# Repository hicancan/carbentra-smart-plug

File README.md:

<div align="center">

> 2026-10-01 classroom upgrade: the sole multi-device Edge and contract authority moved to `carbentra-campus-platform/edge` and `packages/iot-contract`. This repository owns Plug hardware, firmware and physical qualification facts. New local ON uses the same commissioning/load/feedback/dwell guards; actual presses establish a15-minute manual hold. The default target still disables actuation. Historical broker/PDF evidence does not automatically validate upgraded shared sources.

# CARBENTRA Plug

### 面向校园能源编排的 AIoT 边缘智能插座

**让普通用电设备拥有可感知、可判断、可执行、可验证的能源接口。**

[English](README_EN.md) ·
[机械工程](mechanical/rev_b/) ·
[电气工程](electronics/rev_b/integrated/) ·
[固件](firmware/) ·
[边缘服务](edge/) ·
[发布证据](release/)

</div>

本机数字验证与源码摘要见 [交付入口](release/START_HERE.md)。GitHub 徽章展示远端工作流状态；物理放行条件独立保留。

<p align="center">
  
</p>

<p align="center">
  <sub>CARBENTRA Plug Rev B · 本地数字验证快照 · 实物尚未验证</sub>
</p>

---

## 一只插座，让普通负载进入可编排能源系统

CARBENTRA Plug 是 CARBENTRA 产品体系的第一个设备终端。

它把传统电器接入一条完整的设备级闭环：

> **感知 → 校验 → 判断 → 执行 → 验证 → 回传**

电压、电流、功率、能量与温度构成设备状态；本地策略决定动作是否具备执行条件；输出反馈确认物理结果；边缘侧持久运输这些事实，平台统一完成资产绑定、预测、约束策略和能碳核算。

当一台设备接入 CARBENTRA Plug，它同时获得联网能力、可观测状态、受约束执行能力，以及一个能够被上层能源系统持续理解的数字接口。

### 四项核心能力

| 能力 | 设备侧职责 |
| --- | --- |
| **感知** | 采集电压、电流、功率、能量、板温与输出状态 |
| **保护** | 本地故障、负载档案、命令时效、序列和物理边界共同参与决策 |
| **执行** | 在本地许可通过后完成受控开关动作 |
| **验证** | 独立读取输出侧状态，把真实结果送回下一轮控制 |

**云端负责全局智能，设备守住物理边界。**

---

## 产品一览

| 项目 | Rev B 数字工程基线 |
| --- | --- |
| 产品名称 | **CARBENTRA Plug** |
| 工程型号 | **CARBENTRA-P16-EVT-B** |
| 名义外形 | **108 × 93 × 65 mm** |
| 主 PCB | **100 × 85 mm，四层** |
| 主控 | **ESP32-C3-WROOM-02U** |
| 电能计量 | **ATM90E26 + 隔离 SPI + 1 mΩ 四端分流器** |
| 机械系统 | **71 个物理机械零件** |
| 主板电气项 | **101 个电气项 + 4 个安装位** |
| 网络链路 | **Wi-Fi + MQTT 双向 TLS** 参考实现 |
| 目标接口 | **单路 220 VAC / 16 A 级设计目标** |
| 当前阶段 | **Rev B 数字工程完成，进入实物 EVT（工程验证样机）前验证阶段** |

<p align="center">
  
</p>

外壳、插孔、后部插脚、本地按钮、状态指示、主板空间、保护器件与温度拾取结构都建立在同一套工程坐标系中，并贯通 FreeCAD、KiCad、Blender 与系统装配导出。

---

# 01 · 机械系统 — 让产品在真实空间里成立

Rev B 机械工程覆盖插接结构、保护门、L/N/PE 导电路径、保险与热保护安装、PCB、远端温度拾取、后部插脚和外壳装配。

## 六视图

六视图给出产品的完整外形关系。当前工程同时提供可编辑 FreeCAD 源、STEP 总装、独立零件、公共坐标系网格、装配边界和机构检查记录。

## 爆炸结构

从外到内依次可以看到：

- 前后壳体与装配结构；
- 插孔保护门与接触机构；
- L / N / PE 导电路径；
- 保险与热保护部件；
- 四层主 PCB；
- 远端温度拾取头；
- 后部插脚与内部端接。

### 6 秒爆炸动画

<p align="center"><sub>点击动画预览可打开原始 MP4。</sub></p>

## 剖视图

剖视图展示机械插接结构、电源路径、主板、保护器件与感知部件在封闭体积中的真实相对关系，并与系统总装使用同一坐标基准。

工程源文件：

- [FreeCAD 系统总装](mechanical/rev_b/CARBENTRA-P16-EVT-B_system_assembly.FCStd)
- [机械 STEP](mechanical/rev_b/CARBENTRA-P16-EVT-B_mechanical.step)
- [详细系统 STEP](mechanical/rev_b/CARBENTRA-P16-EVT-B_system_detailed.step)
- [机械验证摘要](mechanical/rev_b/VALIDATION_SUMMARY.md)

---

# 02 · 电气系统 — 把计量、控制、保护与反馈收进同一块主板

CARBENTRA Plug 的电气设计围绕一条明确主线展开：

> **测得准 · 隔得开 · 控得住 · 看得到结果 · 故障时保留本地保护**

<p align="center">
  
</p>

Rev B 已经整合以下功能域：

- IRM-10-5 隔离 5 V 电源与 AP63203 3.3 V 逻辑电源；
- ESP32-C3 主控、编程接口、本地按钮、状态指示与外置天线接口；
- ATM90E26 电能计量链路、1 mΩ 四端分流器与隔离 SPI；
- 输出侧 AC presence 独立反馈；
- 远端 TMP302 温度阈值链路、锁存与本地物理复位；
- 主保险、热保护、继电器与输出路径；
- 连续 PE 保护导体路径。

## 原理图

**点击上图打开完整原理图 PDF。**

README 总览采用中文功能页名称；元件位号、网络名与工程信号名保留 KiCad 原始命名，方便直接对应设计源文件。

六个功能页面：

[系统总览](electronics/rev_b/integrated/exports/integrated.svg) ·
[主控与通信](electronics/rev_b/integrated/exports/integrated-1%20controller.svg) ·
[电能计量](electronics/rev_b/integrated/exports/integrated-2%20meter.svg) ·
[输出状态反馈](electronics/rev_b/integrated/exports/integrated-3%20feedback.svg) ·
[热保护链](electronics/rev_b/integrated/exports/integrated-4%20thermal.svg) ·
[装配与一级保护](electronics/rev_b/integrated/exports/integrated-5%20assembly%20protection.svg)

KiCad 原生工程：

[`electronics/rev_b/integrated/`](electronics/rev_b/integrated/)

## 四层 PCB

Rev B 主板采用 **100 × 85 mm 四层设计**。当前数字检查记录：

- DRC 违规：**0**
- 未连接项：**0**
- 封装错误：**0**
- ERC 错误 / 警告：**0 / 0**
- 原理图—PCB 独立引脚键对照：**321 / 321 一致**

上图按照 **顶层 F.Cu / 内层一 In1.Cu / 内层二 In2.Cu / 底层 B.Cu** 展示当前铜层。点击可打开完整铜层审阅 PDF。

## PCB 装配

PCB 视觉装配直接由当前 ECAD 导出进入机械总装与 Blender 展示场景，实现原理图、PCB、机械结构和视觉资产之间的连续追踪。

进一步查看：

- [KiCad 原生工程](electronics/rev_b/integrated/integrated.kicad_pro)
- [电气 BOM](electronics/rev_b/integrated/electrical_bom.csv)
- [电气设计定义](electronics/rev_b/integrated/ELECTRICAL_SOURCE.md)
- [功率与电流复核](electronics/rev_b/integrated/POWER_CURRENT_REVIEW.md)
- [最终电气验证摘要](electronics/rev_b/integrated/validation/final_summary.json)

---

# 03 · 固件控制 — 把每一次物理动作放进本地安全上下文

CARBENTRA Plug 会在设备端重新判断每一条控制请求。

控制链依次检查：

- 设备身份与目标；
- 命令时间边界与 TTL；
- 命令序列与重放；
- 当前负载档案；
- 本地故障锁存；
- 计量数据有效性；
- 动作间隔与当前物理状态；
- 输出反馈与请求状态的一致性。

### 三条核心原则

1. **本地安全拥有最高执行优先级。**
2. **过期、重放、错目标和异常格式命令直接拒绝。**
3. **未知或未批准负载进入仅监测状态。**

当前固件代码已经覆盖：

- C 策略核心；
- ATM90E26 采集与完整性检查；
- TMP102 板温采集；
- AC presence 边沿反馈；
- Wi-Fi 重连；
- BLE 安全配网路径；
- MQTT 双向 TLS；
- retained 消息、分片、长度、类型与重复键边界检查；
- NVS 持久命令序号；
- 有界 RAM 遥测缓冲；
- 边缘侧持久化回执语义。

## 可复现软件检查

```powershell
uv venv --python 3.12
uv sync --locked
$env:CARBENTRA_PLATFORM_ROOT='D:\code\github\hicancan\carbentra-suite\carbentra-campus-platform'
pwsh -NoProfile -File scripts/check_windows.ps1 -OutputDirectory 'D:\Temp\codex\carbentra-plug-check' -BuildTarget
```

本机环境、原生 CAD 重建顺序与工具路径见 [Windows 开发说明](docs/WINDOWS_DEVELOPMENT.md)。

Windows 入口会自动编译真实 Switch C 解码器，并将它与三个 Plug C 验证器
一起传入共享 Edge 的 `--release` 门禁。默认从同级的共享平台及 Switch 仓取源；
不同目录可传 `-PlatformRoot`、`-SwitchRoot`。编译入口是共享平台的
`edge/tests/c/switch_command_decoder.c`，链接 Switch 的
`firmware/core/switch_core.c`、`firmware/main/command_json.c` 与 SDK 固定版本
cJSON，构建记录保存源文件及程序 SHA-256。该程序只解析命令行 JSON，
退出码 0/1 分别表示接受/拒绝，没有设备或网络操作。需要复用已编译程序时，
仍可显式传 `-SwitchCommandTestBinary`；缺失或失败不会降级为跳过。
Linux `run_development_checks.sh` 和独立完整 release 验证器仍要求
`CARBENTRA_SWITCH_COMMAND_TEST_BINARY`。CAD 或场景改变时，再加
`-CheckNativeCAD -RenderGPU`；Windows 通过不会自动更新历史 Linux/CAD 证明。

[本次固件复验](firmware/remediation-report.json)记录全新 ESP-IDF 5.4.3 目标构建、
host 安全回归和新增共享解码器门禁的传递检查。它不修改原有实物 HOLD 状态，
也不把历史 CAD/制造报告重新标为本次运行。

当前仓库已验证：

- 唯一 C 本地保护核心，**45** 个策略用例；
- 边缘发布门禁记录 OS 专属排除与互补验证，当前测试数量见 firmware/evidence/shared-edge-validation.json；
- **10,000** 次本地故障优先级不变量检查；
- 协议 / 计量复位 / 链路卡滞回归；
- 输出反馈判定测试；
- 已配置 GitHub Actions Windows 主机门禁和 ESP32-C3 目标构建；远端执行状态以 Actions 记录为准。

ESP32-C3 当前源码已使用官方 ESP-IDF 5.4.3 重新构建，默认继电器禁用、证书有效期校验启用；源码与产物摘要见 firmware/validation.json。真实硬件验证仍为 HOLD。

---

# 04 · 边缘协同 — 把设备事实沉淀成楼宇侧状态

设备把测量与执行结果交给边缘节点，边缘节点将它们组织成可以持续协调的楼宇侧状态。

共享平台仓库中的边缘服务提供：

- MQTT 设备适配；
- 允许清单与设备身份校验；
- SQLite WAL 持久化；
- 启动纪元 + 序号去重；
- 持久化回执；
- 控制回执保存；
- 带重试和冲突隔离的 HTTP outbox；
- 持久命令 inbox、租约、过期/重放守卫和独立物理放行门；
- 源摘要绑定的真实软件 broker / 平台联调。预测、调度和核算只有平台一份实现。

一条设备遥测在成功落库后返回持久化回执，由此可以清晰区分“消息已到达 MQTT 消息代理”和“数据已进入边缘状态库”。

[查看边缘参考服务](edge/README.md)

---

# 05 · 云边端协同 — 从一个设备节点扩展到一组可协调负载

当设备端的感知、执行和反馈闭环成立，多台 CARBENTRA Plug 就可以进入更高层的能源协调。

系统分工：

- **CARBENTRA Plug**：感知、保护、执行、验证；
- **CARBENTRA Edge**：合同校验、持久收据、重试运输、命令网关；
- **CARBENTRA Cloud**：负荷预测、约束策略评估、全局调度；
- **CARBENTRA Twin**：映射设备、空间、能耗、碳排与执行状态。

> **一只 Plug 让一台设备可被控制；一组 Plug 让一片负载可以被协同。**

CARBENTRA Plug 位于能源算法与真实物理设备之间，把调度策略落到最后一米，并把执行结果重新送回系统。

---

## 工程进度

| 领域 | 当前状态 |
| --- | --- |
| 产品定义 | ✅ CARBENTRA Plug Rev B 数字基线 |
| 机械 CAD | ✅ 原生 CAD + STEP + 装配 / 机构 / 连通性证据 |
| 电气设计 | ✅ 六页原理图 + 四层 PCB + ERC / DRC 数字检查 |
| 固件主机逻辑 | ✅ 策略、协议、反馈、计量回归测试 |
| 边缘参考服务 | ✅ 严格合同、持久运输、mTLS 虚拟设备闭环 |
| 视觉 / 数字孪生资产 | ✅ Blender、GLB、渲染、爆炸动画 |
| ESP32-C3 新版目标二进制 | ✅ 官方 ESP-IDF 5.4.3 当前源码实际构建，继电器禁用 |
| 实物 EVT（工程验证样机） | ⏳ 下一阶段 |
| 逐台计量标定 | ⏳ 实物阶段 |
| 16 A 温升 / 故障验证 | ⏳ 实物阶段 |
| 绝缘 / EMC / 浪涌 / 安规 | ⏳ 专业审查与试验阶段 |
| 校园现场闭环 | ⏳ EVT 与安全放行后进入 |

完整工程放行条件：

[`docs/ENGINEERING_RELEASE_GATES.md`](docs/ENGINEERING_RELEASE_GATES.md)

---

## 打开工程

### 机械工程

```text
mechanical/rev_b/
├── CARBENTRA-P16-EVT-B.FCStd
├── CARBENTRA-P16-EVT-B_mechanical.step
├── CARBENTRA-P16-EVT-B_system_assembly.FCStd
├── CARBENTRA-P16-EVT-B_system_assembly.step
├── CARBENTRA-P16-EVT-B_system_detailed.step
├── parts/
├── meshes/
└── validation reports...
```

### 电气工程

```text
electronics/rev_b/integrated/
├── integrated.kicad_pro
├── integrated.kicad_sch
├── integrated.kicad_pcb
├── electrical_bom.csv
├── electrical_manifest.json
├── exports/
└── validation/
```

### 固件与边缘服务

```text
firmware/
├── core/
├── main/
├── tests/
├── tools/
└── validation.json

edge/
├── README.md        # shared implementation: carbentra-campus-platform/edge
└── PROVENANCE.json  # migration record
```

### 视觉与数字孪生

```text
visuals/rev_b/
├── carbentra_studio.blend
├── carbentra_animation.blend
├── exports/
│   ├── carbentra_assembly.glb
│   └── carbentra_twin_light.glb
├── renders/
└── animation/
```

---

## 仓库结构

```text
carbentra-smart-plug/
├── mechanical/      # CAD、STEP、零件、机构与装配检查
├── electronics/     # KiCad 原理图、PCB、BOM、电气验证
├── firmware/        # ESP32-C3 源码、策略、计量、网络与主机测试
├── edge/            # 平台共享 Edge 的迁移说明与来源记录
├── visuals/         # Blender、渲染、GLB、动画
├── docs/            # 系统契约、品牌体系与平台叙事
├── tests/           # 策略参考测试
├── scripts/         # 验证与发布工具
└── release/         # 数字工程发布证据与审阅材料
```

按照工程审阅顺序阅读时，可以从 [`release/START_HERE.md`](release/START_HERE.md) 开始。

---

## 从数字工程走向实物 EVT

当前 Rev B 已经把机械、电气、固件、边缘服务和视觉资产收敛到同一套数字工程基线。下一阶段将把这些设计结论逐项落到实物验证：

- 目标市场对应的插头 / 插座标准确认；
- 实际爬电距离、空气间隙与绝缘结构审核；
- 外壳材料与异常工况验证；
- 预期故障电流与保护配合；
- 16 A 封闭温升与连接点发热试验；
- 插接量规、接触力、寿命、保持力与保护门验证；
- 不同负载类型的浪涌与继电器开断能力测试；
- 电压、电流、功率、能量逐台可溯源标定；
- 浪涌 / EFT / EMC / RF 集成测试；
- 生产级设备身份、安全启动、升级与密钥配置；
- 受控实物 EVT 与真实场景闭环验证。

> [!WARNING]
> **220 VAC / 16 A 级接口目前属于设计目标。实物额定能力、制造放行与产品合规将在上述验证完成后确定。**

---

## 项目与品牌

**CARBENTRA Plug** 是 CARBENTRA 产品体系中的首个设备终端。

```text
碳迹未来
└── CARBENTRA
    ├── CARBENTRA Plug      ← 本仓库
    ├── CARBENTRA Sense
    ├── CARBENTRA Edge
    ├── CARBENTRA Cloud
    └── CARBENTRA Twin
```

比赛 / 项目名称：

> **碳迹未来——基于 AIoT 云边端协同的高校智慧能碳管理平台**

平台英文描述：

> **CARBENTRA — AIoT Campus Energy Orchestration Platform**

完整平台叙事：

[**docs/PLATFORM_OVERVIEW.md**](docs/PLATFORM_OVERVIEW.md)

---

<div align="center">

# CARBENTRA Plug

### **Sense · Protect · Execute · Verify**

**让普通设备进入可编排的能源系统。**

[English README](README_EN.md)

</div>

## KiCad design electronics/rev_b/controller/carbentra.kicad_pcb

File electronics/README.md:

# CARBENTRA electronic development release

## What exists

Editable KiCad 9 schematic and two-layer 72×68 mm PCB; upstream-symbol-derived pin geometry; 33 placed electrical components plus 4 mounting holes (37 footprints); real net assignments; fully connected isolated low-voltage routing (digital connectivity only); true KiCad ERC/DRC reports; BOM candidate sources; board/package STEP, FreeCAD and OBJ; regenerated PDF/SVG review drawings. This is a **development source release with FABRICATION HOLD**, not a finished appliance circuit or a safe prototype to energize.

Main controller: ESP32-C3-WROOM-02U-N4 with external antenna connector, 5 V isolated supply candidate, 3.3 V synchronous buck, relay MOSFET/flyback network and digital board temperature sensor, physical local pushbutton and status LED. GPIO 18/19 are allocated to these controls, so native USB is not available on this revision. Main switching candidate is TE RT314005 5 V coil. Mains input/output/fused-auxiliary nets are intentionally unrouted. The right-hand LV routing region is digitally connected and DRC-checked, not a verified EMC/power integrity layout.

A real external antenna candidate and a mechanical pocket are defined in `PROTECTION_AND_RF.md`. Check module integration approvals and qualify range with enclosure/contact metal. The MCU variant is 02U, with an external antenna.

## Files

- `carbentra.kicad_sch`, `.kicad_pcb`, `.kicad_pro`, `.kicad_dru`: editable source and preliminary constraints
- `CARBENTRA.kicad_sym`, `sym-lib-table`: local symbols, flattened from installed KiCad library for portability
- `circuit_manifest.json`: machine-readable pins, nets, placements and schematic positions
- `bom.csv`: candidates, NOT a purchase-approved BOM; passives require precise grade/voltage/package selection
- `METERING_DESIGN.md`: substantive isolated metering boundary, pin map and sizing; daughterboard NOT implemented
- `validation/`: actual ERC, DRC, routing and geometric validation outputs
- `exports/`: review-only models/drawings
- `scripts/build_electronics.py`: regenerate source (overwrites board routing)
- `scripts/route_lv.py`: attempt LV routing, always follow with real DRC
- `scripts/export_geometry.py`: nominal package envelopes + board/footprint pad visualization

## Functional and power assumptions

IRM-03-5 candidate supplies 5 V/0.6 A. A 0.403 W relay coil consumes about 81 mA. An assumed 0.5 A peak 3.3 V controller load at 85% buck efficiency draws 388 mA from 5 V, leaving about 131 mA before other loads and supply derating. This is a preliminary budget, not measured. Include metering isolation power and all transients before final selection; verify rail dips during simultaneous radio transmission/relay actuation. Buck capacitor effective capacitance must account for DC bias, and high-current loop/switch-node layout requires review.

AP63203 pins: 1 FB → 3.3 V; 2 EN → 5 V; 3 IN → 5 V; 4 GND; 5 SW; 6 BST. Q1 is AO3400A, with manufacturer maximum RDS(on) of 48 mΩ at 2.5 V gate drive. Its pins are 1 gate, 2 source to ground, 3 drain to coil-low. D1 cathode connects to 5 V and anode to coil-low. R2 holds the gate low when the MCU is high-impedance; it is not an independent safety channel. Relay contact 11 is common, 14 is normally open, and 12 is externally unused but remains a hazardous live terminal when the relay is de-energized; it is assigned L_NC_UNUSED for clearance checking. A welded contact cannot be made safe by firmware.

Cold boot / loss of control power de-energizes this monostable relay. Runtime unknown-load handling is monitor-only; stale data rejects new automatic commands and holds the commissioned state, as specified in the system reference model. Hardware fault interruption, watchdog policy and power-restoration behavior must be commissioned by load category. This board does not implement a universal abrupt shutdown policy.

## Mains and PE

Target: 220 V nominal, 16 A-class single polarized socket. Actual continuous current, branch protection, terminal rating, contact category and operating temperature remain unqualified. **16 A resistive relay rating does not establish air-conditioner/compressor/motor, transformer or capacitive-inrush capability.** Profile software cannot uprate contacts or copper. Unknown loads are monitor-only for automatic energy management; known load categories still require validated hardware limits.

J1, J2 and J5 use Phoenix MKDS 3/2-5.08, part 1711725, with the matching KiCad footprint. Its 24 A nominal rating is a component rating, not this product's released continuous-current rating. Confirm the final conductor, torque, support, temperature rise and strain relief. High-current copper is absent: copper weight, width, neck-downs, solder joints and fault let-through must be engineered before routing. Do not bridge the airwires and energize.

Real main/auxiliary fuse and independent thermal-cutoff candidates are now dimensioned in `PROTECTION_AND_RF.md` and allocated mechanically; their electrical/harness integration and coordination are not validated. Surge network and any required snubber remain incomplete. They require ratings, layout, failure-mode analysis and system-level testing. A fuse is not an over-temperature sensor; a MOV alone is not complete surge protection.

PE bypasses this PCB in an uninterrupted stamped/wired protective path and must never be switched, fused or routed through the MCU ground. Mechanical PE continuity solids are not proof of actual earth-bond resistance, retention or contact force. Never assume N is safe to touch; polarity/reversal fault analysis and all-pole disconnection requirements depend on final product category.

## Review gates before any hardware build

- [ ] Choose target jurisdiction, plug/socket dimensional standard, accessible-part class, temperature range and required compliance tests
- [ ] Complete all mains/protection/metrology circuits and independent thermal safety; produce fault tree and critical-component list
- [ ] Resolve all KiCad unconnected nets and DRC violations without suppressing safety failures
- [ ] Verify every manufacturer pin/footprint drawing, exact suffix, BOM source and symbol connectivity independently
- [ ] Confirm required clearance/creepage from applicable standards; 8 mm rule is an explicitly preliminary engineering target, not a compliance conclusion
- [ ] Validate all copper currents/temperature rises, conductor/terminal retention, PE bond and short-circuit withstand
- [ ] Complete external antenna and metering daughterboard mechanical allocations, wiring paths, connectors and controls
- [ ] Test surge/EFT/ESD/EMI, dielectric/impulse, leakage, abnormal temperature, relay endurance and welded-contact behavior in a qualified lab
- [ ] Verify watchdog, brownout, cold-boot de-energization, stale-data command rejection, offline commissioned-state hold and secure signed firmware behavior
- [ ] Release only after independent electrical/safety review and documented manufacturer acceptance

No Gerber/drill set is supplied because it would misleadingly imply fabrication readiness. Reports may be clean in one domain while the design remains incomplete and unsafe to power.

## Final digital verification

ERC: **0 errors, 0 warnings**. PCB DRC: **0 geometric violations**, **0 low-voltage airwires**, **9 intentional mains-domain airwires**. All 104 assigned pins match the exported schematic netlist and PCB pads. See `validation/final_summary.json` and the complete, unfiltered reports. DRC success does not remove fabrication hold: the mains circuit remains physically incomplete and the metering daughterboard is not implemented.

The final board has 729 routed segments, 85 vias and 2 ground zones. These establish digital connectivity, not safe current capacity, EMC performance, transient integrity, or protection behavior. No embedded firmware has been flashed or exercised on hardware.

KiCad library symbol geometry is attributed to the KiCad Community under its library licence and design exception; see `KICAD_LIBRARY_LICENSE.txt`.

## Rebuild and system interfaces

Run `bash scripts/rebuild.sh` with KiCad 9 and its Python bindings installed. It regenerates placement and schematic, checks fixed geometry, then replays the reviewed completed-LV copper recipe. Do not rerun the experimental autorouting helpers on the finished board. Exporting package STEP/OBJ also requires FreeCAD Python; `scripts/export_geometry.py` handles it.

For the Wi-Fi/BLE deployment boundary, sensor ownership and exact runtime unknown/stale-data behavior, see [wireless networking and sensors](../docs/system/network-and-sensors.md) and [system requirements](../docs/system/README.md). The PCB includes board temperature sensing, not a complete hot-contact telemetry path. Independent relay/output-state feedback and the metering daughterboard remain incomplete.

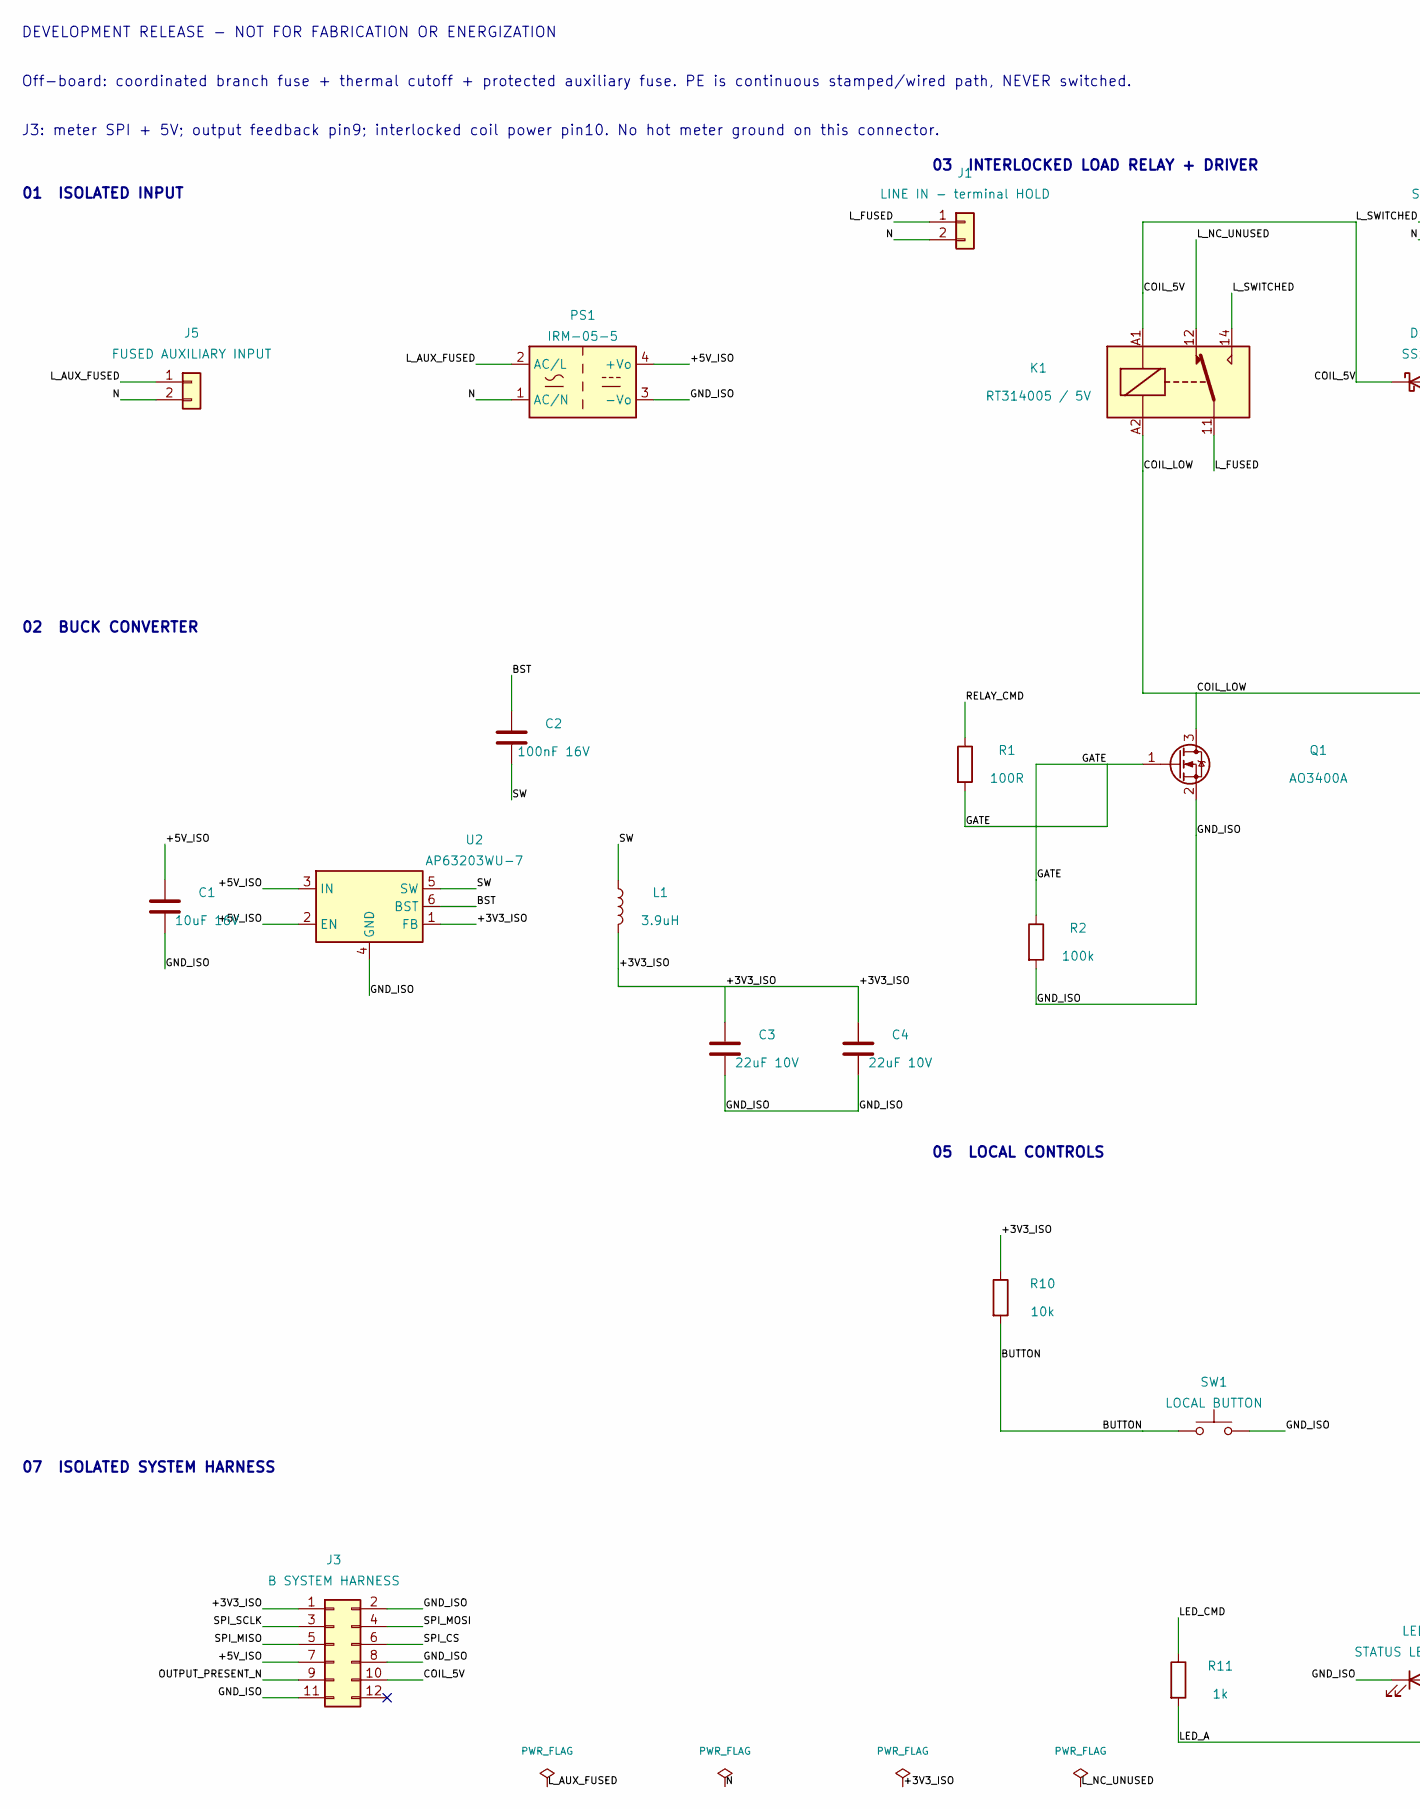
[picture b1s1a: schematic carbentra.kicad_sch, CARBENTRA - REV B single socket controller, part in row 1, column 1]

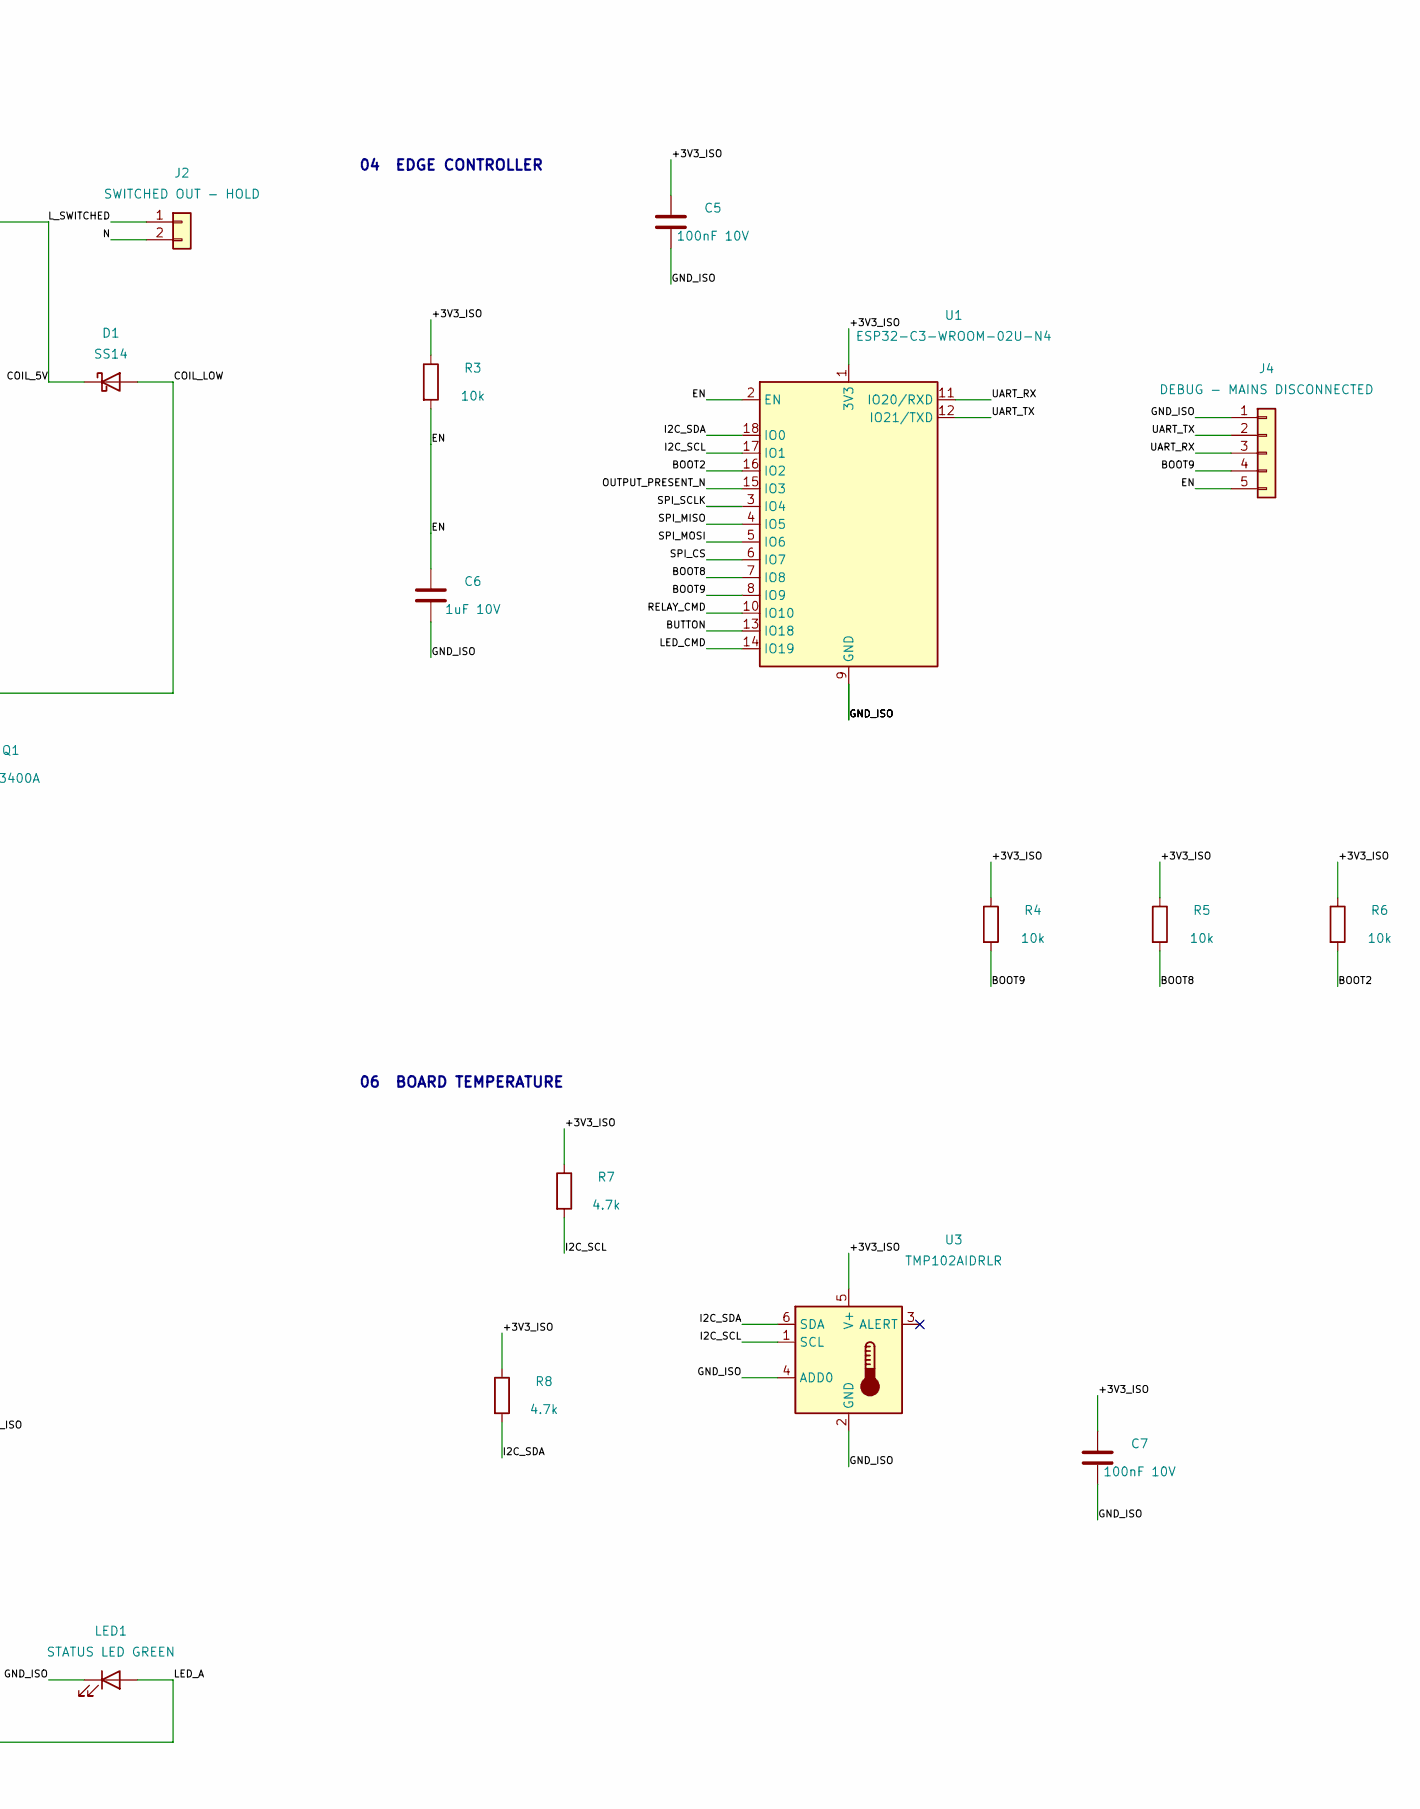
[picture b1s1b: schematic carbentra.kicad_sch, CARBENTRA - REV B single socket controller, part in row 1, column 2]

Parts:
C1: 10uF 16V; C_0805_2012Metric
C2: 100nF 16V; C_0805_2012Metric
C3, C4: 22uF 10V; C_0805_2012Metric
C5, C7: 100nF 10V; C_0805_2012Metric
C6: 1uF 10V; C_0805_2012Metric
D1: SS14; D_SMA
J1: LINE IN - terminal HOLD; TerminalBlock_Phoenix_MKDS-3-2-5.08_1x02_P5.08mm_Horizontal
J2: SWITCHED OUT - HOLD; TerminalBlock_Phoenix_MKDS-3-2-5.08_1x02_P5.08mm_Horizontal
J3: B SYSTEM HARNESS; PinHeader_2x06_P2.54mm_Vertical
J4: DEBUG - MAINS DISCONNECTED; PinHeader_1x05_P2.54mm_Vertical
J5: FUSED AUXILIARY INPUT; TerminalBlock_Phoenix_MKDS-3-2-5.08_1x02_P5.08mm_Horizontal
K1: RT314005 / 5V; Relay_SPDT_Schrack-RT1-16A-FormC_RM5mm
L1: 3.9uH; L_Bourns-SRN4018
LED1: STATUS LED GREEN; LED_D3.0mm
PS1: IRM-05-5; Converter_ACDC_MeanWell_IRM-05-xx_THT
Q1: AO3400A; SOT-23
R1: 100R; R_0603_1608Metric
R2: 100k; R_0603_1608Metric
R3, R4, R5, R6, R10: 10k; R_0603_1608Metric
R7, R8: 4.7k; R_0603_1608Metric
R11: 1k; R_0603_1608Metric
SW1: LOCAL BUTTON; SW_PUSH_6mm
U1: ESP32-C3-WROOM-02U-N4; ESP32-C3-WROOM-02U
U2: AP63203WU-7; TSOT-23-6
U3: TMP102AIDRLR; SOT-563

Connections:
+3V3_ISO: C3.1, C4.1, C5.1, C7.1, J3.1, L1.2, R3.1, R4.1, R5.1, R6.1, R7.1, R8.1, R10.1, U1.1 (3V3), U2.1 (FB), U3.5 (V+)
+5V_ISO: C1.1, J3.7, PS1.4 (+Vo), U2.2 (EN), U2.3 (IN)
BOOT2: R6.2, U1.16 (IO2)
BOOT8: R5.2, U1.7 (IO8)
BOOT9: J4.4, R4.2, U1.8 (IO9)
BST: C2.1, U2.6 (BST)
BUTTON: R10.2, SW1.1, U1.13 (IO18)
COIL_5V: D1.1 (K), J3.10, K1.A1
COIL_LOW: D1.2 (A), K1.A2, Q1.3 (D)
EN: C6.1, J4.5, R3.2, U1.2 (EN)
GATE: Q1.1 (G), R1.2, R2.1
GND_ISO: C1.2, C3.2, C4.2, C5.2, C6.2, C7.2, J3.2, J3.8, J3.11, J4.1, LED1.1 (K), PS1.3 (-Vo), Q1.2 (S), R2.2, SW1.2, U1.9 (GND), U1.19 (GND), U2.4 (GND), U3.2 (GND), U3.4 (ADD0)
I2C_SCL: R7.2, U1.17 (IO1), U3.1 (SCL)
I2C_SDA: R8.2, U1.18 (IO0), U3.6 (SDA)
LED_A: LED1.2 (A), R11.2
LED_CMD: R11.1, U1.14 (IO19)
L_AUX_FUSED: J5.1, PS1.2 (AC/L)
L_FUSED: J1.1, K1.11
L_NC_UNUSED: K1.12
L_SWITCHED: J2.1, K1.14
N: J1.2, J2.2, J5.2, PS1.1 (AC/N)
OUTPUT_PRESENT_N: J3.9, U1.15 (IO3)
RELAY_CMD: R1.1, U1.10 (IO10)
SPI_CS: J3.6, U1.6 (IO7)
SPI_MISO: J3.5, U1.4 (IO5)
SPI_MOSI: J3.4, U1.5 (IO6)
SPI_SCLK: J3.3, U1.3 (IO4)
SW: C2.2, L1.1, U2.5 (SW)
UART_RX: J4.3, U1.11 (IO20/RXD)
UART_TX: J4.2, U1.12 (IO21/TXD)

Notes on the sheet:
DEVELOPMENT RELEASE - NOT FOR FABRICATION OR ENERGIZATION
Off-board: coordinated branch fuse + thermal cutoff + protected auxiliary fuse. PE is continuous stamped/wired path, NEVER switched.
J3: meter SPI + 5V; output feedback pin9; interlocked coil power pin10. No hot meter ground on this connector.
01 ISOLATED INPUT
02 BUCK CONVERTER
03 INTERLOCKED LOAD RELAY + DRIVER
04 EDGE CONTROLLER
05 LOCAL CONTROLS
06 BOARD TEMPERATURE
07 ISOLATED SYSTEM HARNESS

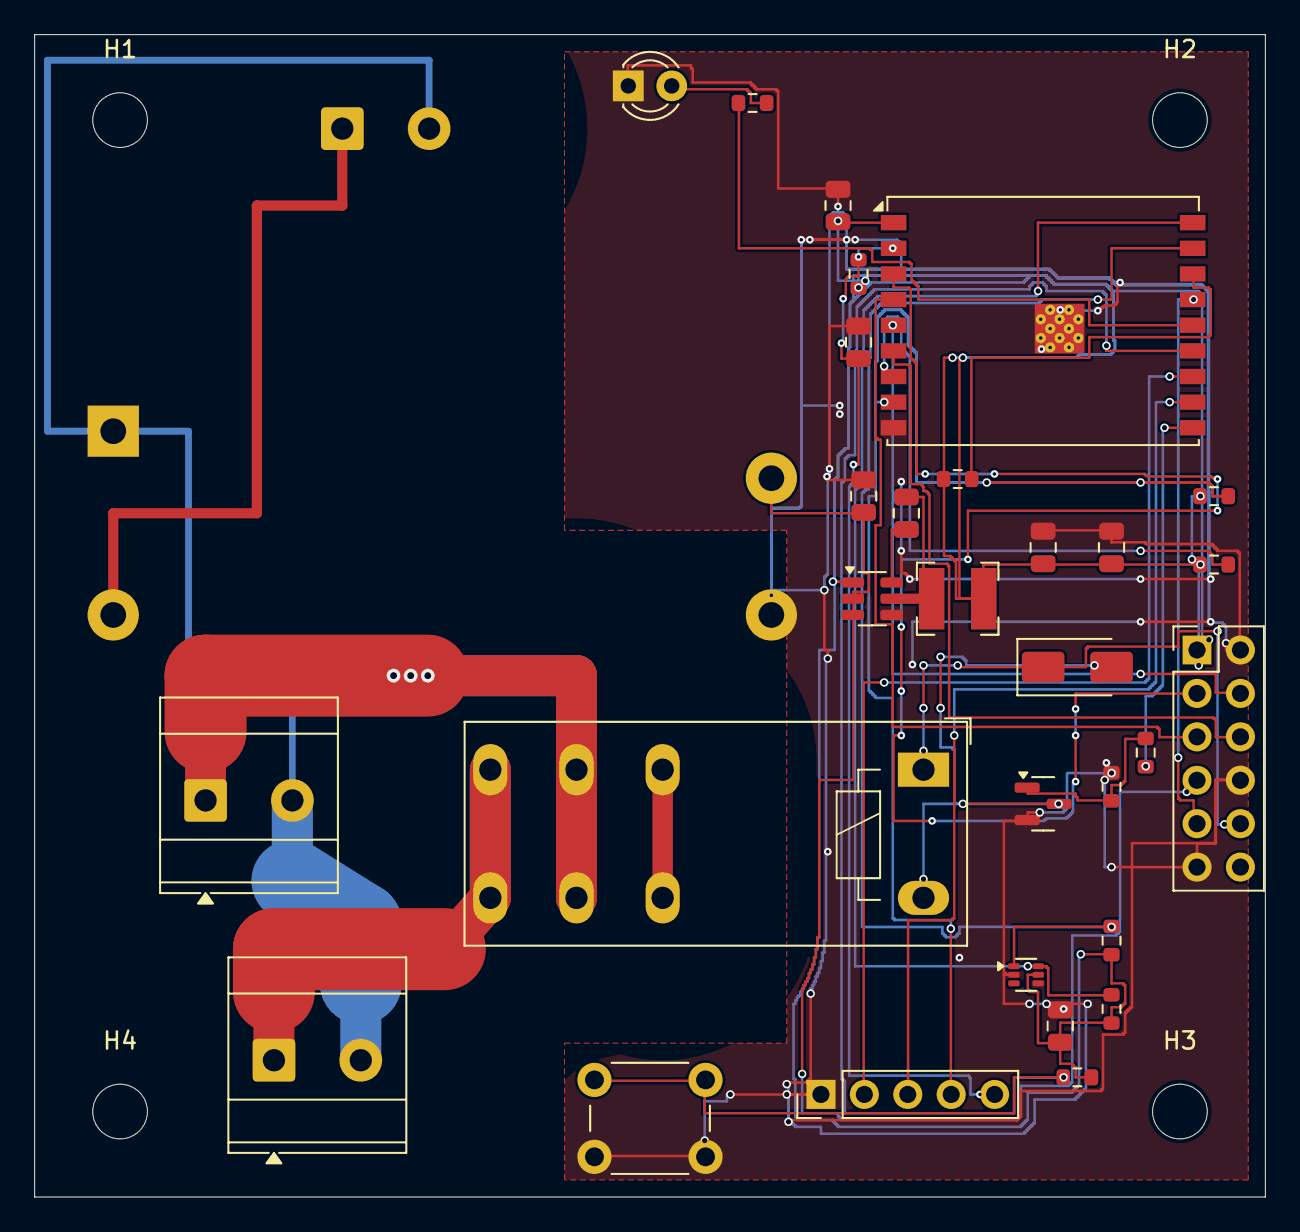
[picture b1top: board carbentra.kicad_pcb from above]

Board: 2 copper layers, 72.0 x 68.0 mm, 36 parts (0 on the bottom side), 29 nets.

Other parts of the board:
H1, H2, H3, H4: MountingHole_3.2mm_M3

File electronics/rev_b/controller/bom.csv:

Reference,Value,Manufacturer part candidate,Footprint,Source URL,Status
PS1,IRM-05-5,IRM-05-5,Converter_ACDC:Converter_ACDC_MeanWell_IRM-05-xx_THT,https://www.meanwell.com/Upload/PDF/IRM-05/IRM-05-SPEC.PDF,"UNRELEASED: verify exact variant, sourcing and application"
K1,RT314005 / 5V,RT314005 / 1-1649328-0,Relay_THT:Relay_SPDT_Schrack-RT1-16A-FormC_RM5mm,https://www.te.com/en/product-1-1649328-0.html,"UNRELEASED: verify exact variant, sourcing and application"
U1,ESP32-C3-WROOM-02U-N4,ESP32-C3-WROOM-02U-N4,RF_Module:ESP32-C3-WROOM-02U,https://www.espressif.com/sites/default/files/documentation/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,"UNRELEASED: verify exact variant, sourcing and application"
U2,AP63203WU-7,AP63203WU-7,Package_TO_SOT_SMD:TSOT-23-6,https://www.diodes.com/datasheet/download/AP63200-AP63201-AP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,"UNRELEASED: verify exact variant, sourcing and application"
L1,3.9uH,SRN4018-3R9M,Inductor_SMD:L_Bourns-SRN4018,https://www.bourns.com/docs/product-datasheets/srn4018.pdf,"UNRELEASED: verify exact variant, sourcing and application"
C1,10uF 16V,GRM21-series candidate,Capacitor_SMD:C_0805_2012Metric,https://www.murata.com/en-us/products/capacitor/ceramiccapacitor,"UNRELEASED: verify exact variant, sourcing and application"
C2,100nF 16V,GRM21-series candidate,Capacitor_SMD:C_0805_2012Metric,https://www.murata.com/en-us/products/capacitor/ceramiccapacitor,"UNRELEASED: verify exact variant, sourcing and application"
C3,22uF 10V,GRM21-series candidate,Capacitor_SMD:C_0805_2012Metric,https://www.murata.com/en-us/products/capacitor/ceramiccapacitor,"UNRELEASED: verify exact variant, sourcing and application"
C4,22uF 10V,GRM21-series candidate,Capacitor_SMD:C_0805_2012Metric,https://www.murata.com/en-us/products/capacitor/ceramiccapacitor,"UNRELEASED: verify exact variant, sourcing and application"
C5,100nF 10V,GRM21-series candidate,Capacitor_SMD:C_0805_2012Metric,https://www.murata.com/en-us/products/capacitor/ceramiccapacitor,"UNRELEASED: verify exact variant, sourcing and application"
Q1,AO3400A,AO3400A,Package_TO_SOT_SMD:SOT-23,https://www.aosmd.com/res/data_sheets/AO3400A.pdf,"UNRELEASED: verify exact variant, sourcing and application"
D1,SS14,SS14,Diode_SMD:D_SMA,https://www.vishay.com/docs/88746/ss12.pdf,"UNRELEASED: verify exact variant, sourcing and application"
R1,100R,RC0603FR-07100RL,Resistor_SMD:R_0603_1608Metric,https://www.yageo.com/en/ProductSearch,"UNRELEASED: verify exact variant, sourcing and application"
R2,100k,RC0603FR-07100KL,Resistor_SMD:R_0603_1608Metric,https://www.yageo.com/en/ProductSearch,"UNRELEASED: verify exact variant, sourcing and application"
R3,10k,RC0603FR-0710KL,Resistor_SMD:R_0603_1608Metric,https://www.yageo.com/en/ProductSearch,"UNRELEASED: verify exact variant, sourcing and application"
C6,1uF 10V,GRM21-series candidate,Capacitor_SMD:C_0805_2012Metric,https://www.murata.com/en-us/products/capacitor/ceramiccapacitor,"UNRELEASED: verify exact variant, sourcing and application"
R4,10k,RC0603FR-0710KL,Resistor_SMD:R_0603_1608Metric,https://www.yageo.com/en/ProductSearch,"UNRELEASED: verify exact variant, sourcing and application"
R5,10k,RC0603FR-0710KL,Resistor_SMD:R_0603_1608Metric,https://www.yageo.com/en/ProductSearch,"UNRELEASED: verify exact variant, sourcing and application"
R6,10k,RC0603FR-0710KL,Resistor_SMD:R_0603_1608Metric,https://www.yageo.com/en/ProductSearch,"UNRELEASED: verify exact variant, sourcing and application"
U3,TMP102AIDRLR,TMP102AIDRLR,Package_TO_SOT_SMD:SOT-563,https://www.ti.com/lit/ds/symlink/tmp102.pdf,"UNRELEASED: verify exact variant, sourcing and application"
R7,4.7k,RC0603FR-074K7L,Resistor_SMD:R_0603_1608Metric,https://www.yageo.com/en/ProductSearch,"UNRELEASED: verify exact variant, sourcing and application"
R8,4.7k,RC0603FR-074K7L,Resistor_SMD:R_0603_1608Metric,https://www.yageo.com/en/ProductSearch,"UNRELEASED: verify exact variant, sourcing and application"
C7,100nF 10V,GRM21-series candidate,Capacitor_SMD:C_0805_2012Metric,https://www.murata.com/en-us/products/capacitor/ceramiccapacitor,"UNRELEASED: verify exact variant, sourcing and application"
J1,LINE IN - terminal HOLD,1711725,TerminalBlock_Phoenix:TerminalBlock_Phoenix_MKDS-3-2-5.08_1x02_P5.08mm_Horizontal,https://www.phoenixcontact.com/en-pc/products/pcb-terminal-b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,"UNRELEASED: verify exact variant, sourcing and application"
J2,SWITCHED OUT - HOLD,1711725,TerminalBlock_Phoenix:TerminalBlock_Phoenix_MKDS-3-2-5.08_1x02_P5.08mm_Horizontal,https://www.phoenixcontact.com/en-pc/products/pcb-terminal-b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,"UNRELEASED: verify exact variant, sourcing and application"
J3,B SYSTEM HARNESS,TSW-106-07-G-D,Connector_PinHeader_2.54mm:PinHeader_2x06_P2.54mm_Vertical,https://www.samtec.com/products/tsw,"UNRELEASED: verify exact variant, sourcing and application"
J4,DEBUG - MAINS DISCONNECTED,Samtec TSW-1xx-07 candidate,Connector_PinHeader_2.54mm:PinHeader_1x05_P2.54mm_Vertical,https://www.samtec.com/products/tsw,"UNRELEASED: verify exact variant, sourcing and application"
J5,FUSED AUXILIARY INPUT,1711725,TerminalBlock_Phoenix:TerminalBlock_Phoenix_MKDS-3-2-5.08_1x02_P5.08mm_Horizontal,https://www.phoenixcontact.com/en-pc/products/pcb-terminal-b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,"UNRELEASED: verify exact variant, sourcing and application"
SW1,LOCAL BUTTON,B3F-1000 candidate,Button_Switch_THT:SW_PUSH_6mm,https://components.omron.com/us-en/products/switches/B3F,"UNRELEASED: verify exact variant, sourcing and application"
LED1,STATUS LED GREEN,WP710A10GD candidate,LED_THT:LED_D3.0mm,https://www.kingbrightusa.com/,"UNRELEASED: verify exact variant, sourcing and application"
R10,10k,RC0603FR-0710KL,Resistor_SMD:R_0603_1608Metric,https://www.yageo.com/en/ProductSearch,"UNRELEASED: verify exact variant, sourcing and application"
R11,1k,RC0603FR-071KL,Resistor_SMD:R_0603_1608Metric,https://www.yageo.com/en/ProductSearch,"UNRELEASED: verify exact variant, sourcing and application"
